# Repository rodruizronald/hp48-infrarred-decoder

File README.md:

# HP-48GX-Infrarred-Signal-Decoder

The HP 48 is a series of graphing calculators capable of communicate with a wireless printer via infrared signals. The protocol used by these calculators, called "Rey Eye", operates in a frequency of 33 kHz. This project aims to replicate a program that runs in an HP 48GX to read an electronic people counter. Reading the counters with a calculator is not practical, and therefore a specific device should be built for this task. To construct such device the project was divided into three parts.

First, the signals emitted by the calculator's program were decoded with an IR sensor conneceted to an oscilloscope and then replicated with an Atmega328p. After decoding the infrared signals, the results were examined to understand better the protocol. This examination provided the required information to code a program capable of reading the infrared signals. Finally, to implement the emitter and receiver code in a functional device, a PCB board was designed.

Although this project focuses on a specific program to read electronic people counter, it can be used as a starting point for others since the communication protocol is the same for all applications.

## Red Eye Protocol

The Red Eye Frame is composed of 15 bits:

* 1.5 start bits.   
* 4 error bits.
* 8 data bits.
* 1.5 stop bits.

Generally, the length of each bit within the frame is 854.5 us, but this value could vary depend on the IR sensor implemented. It is advisable to test with an oscilloscope the output of the sesor before making any assumptions. The logic level of one bit is defined by the position of a high state within the pulse. The high state takes 244 us, time in which the IR Led is switching on and off every 15.15 us (one cycle 30.3 us).

## Prototype

The PCB prototype contains both an IR sensor and LED to implement a bidirectional communication with the electronic counter. Additionally, a wireless LAN module was added to request and get the data remotely. The implementation of this module will be discussed in another repository to maintain this one consistent.

## Software

* Atmel Studio 6.0 - Integrated Development Platform for developing and debugging AVR microcontrollers.
* Eagle PCB Design - PCB layout and schematic design software.

## License

This project is licensed under the MIT License - see the [LICENSE.md](LICENSE.md) file for details.

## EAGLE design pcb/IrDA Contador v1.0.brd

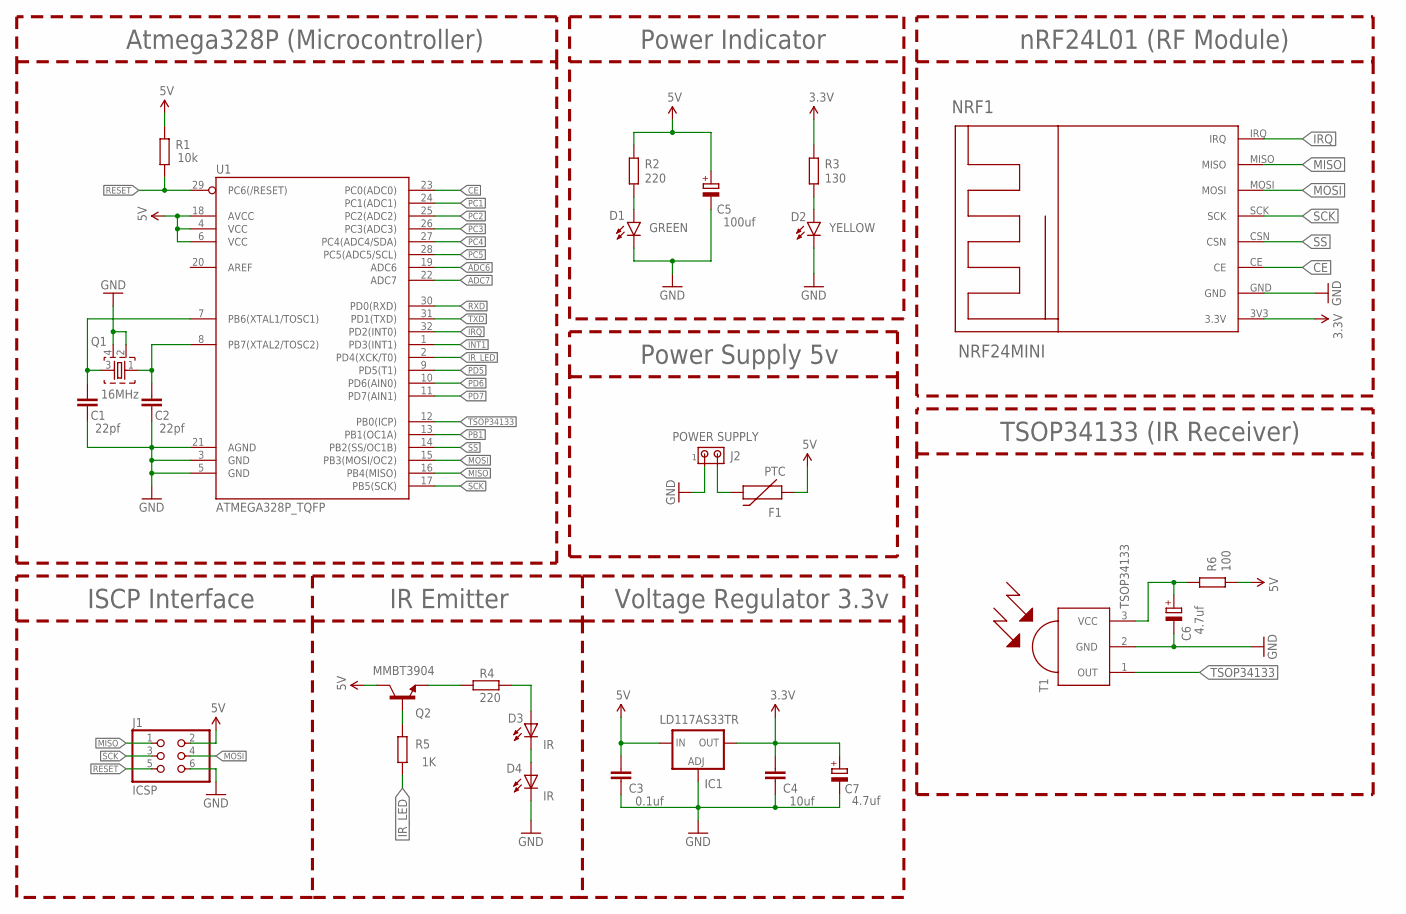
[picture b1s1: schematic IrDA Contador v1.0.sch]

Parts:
C1, C2: 22pf; C0603
C3: 0.1uf; C0603
C4: 10uf; C0603
C5: 100uf; 153CLV-0605
C6, C7: 4.7uf; SMC_A
D1: GREEN; LED-0603
D2: YELLOW; LED-0603
D3, D4: IR; LED5MM
F1: PTC; 0603
IC1: LD117AS33TR; SOT223
J1: ICSP; 2X03
J2: POWER SUPPLY; 1X2MTA
NRF1: NRF24MINI
Q1: 16MHz; FA-20H
Q2: MMBT3904; SOT23-3
R1: 10k; R0603
R2, R4: 220; R0603
R3: 130; R0603
R5: 1K; R0603
R6: 100; R0603
T1: TSOP34133
U1: ATMEGA328P_TQFP; TQFP32-08

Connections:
3.3V: C4.2, C7.+, IC1.4 (OUT), NRF1.3V3 (3.3V), R3.2
5V: C3.2, C5.+, F1.1, IC1.3 (IN), J1.2, Q2.3 (C), R1.2, R2.2, R6.1, U1.4 (VCC), U1.6 (VCC), U1.18 (AVCC)
ADC6: U1.19 (ADC6)
ADC7: U1.22 (ADC7)
CE: NRF1.CE, U1.23 (PC0(ADC0))
GND: C1.1, C2.1, C3.1, C4.1, C5.-, C6.-, C7.-, D1.C, D2.C, D4.K (C), IC1.1 (ADJ), J1.6, J2.1, NRF1.GND, Q1.2, Q1.4, T1.2 (GND), U1.3 (GND), U1.5 (GND), U1.21 (AGND)
INT1: U1.1 (PD3(INT1))
IRQ: NRF1.IRQ, U1.32 (PD2(INT0))
IR_LED: R5.2, U1.2 (PD4(XCK/T0))
MISO: J1.1, NRF1.MISO, U1.16 (PB4(MISO))
MOSI: J1.4, NRF1.MOSI, U1.15 (PB3(MOSI/OC2))
unnamed: D2.A, R3.1
unnamed: C1.2, Q1.3, U1.7 (PB6(XTAL1/TOSC1))
unnamed: C2.2, Q1.1, U1.8 (PB7(XTAL2/TOSC2))
unnamed: D1.A, R2.1
unnamed: Q2.2 (E), R4.2
unnamed: D3.A, R4.1
unnamed: D3.K (C), D4.A
unnamed: C6.+, R6.2, T1.3 (VCC)
unnamed: F1.2, J2.2
unnamed: Q2.1 (B), R5.1
PB1: U1.13 (PB1(OC1A))
PC1: U1.24 (PC1(ADC1))
PC2: U1.25 (PC2(ADC2))
PC3: U1.26 (PC3(ADC3))
PC4: U1.27 (PC4(ADC4/SDA))
PC5: U1.28 (PC5(ADC5/SCL))
PD5: U1.9 (PD5(T1))
PD6: U1.10 (PD6(AIN0))
PD7: U1.11 (PD7(AIN1))
RESET: J1.5, R1.1, U1.29 (PC6(/RESET))
RXD: U1.30 (PD0(RXD))
SCK: J1.3, NRF1.SCK, U1.17 (PB5(SCK))
SS: NRF1.CSN, U1.14 (PB2(SS/OC1B))
TSOP34133: T1.1 (OUT), U1.12 (PB0(ICP))
TXD: U1.31 (PD1(TXD))

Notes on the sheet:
nRF24L01 (RF Module)
Atmega328P (Microcontroller)
TSOP34133 (IR Receiver)
ISCP Interface
Power Supply 5v
Voltage Regulator 3.3v
Power Indicator
IR Emitter

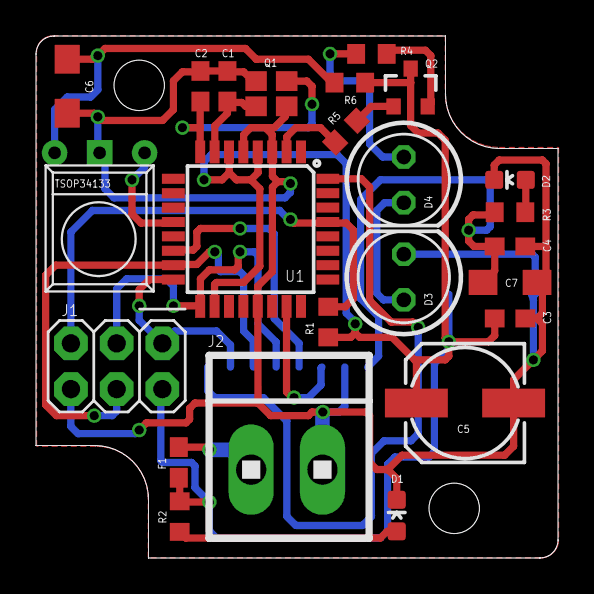
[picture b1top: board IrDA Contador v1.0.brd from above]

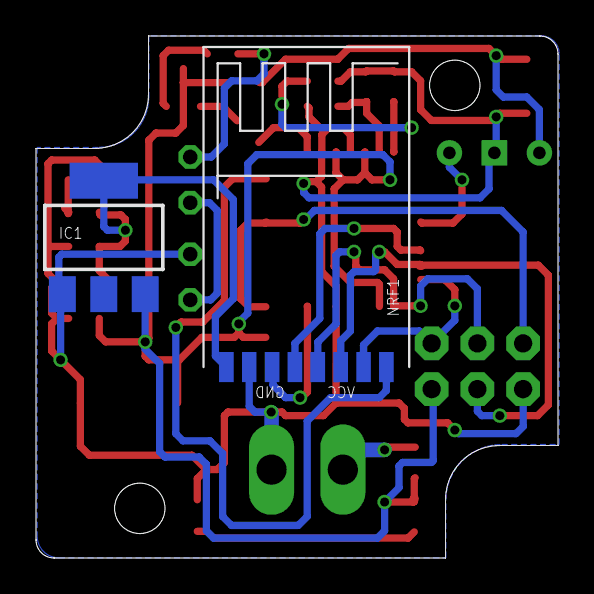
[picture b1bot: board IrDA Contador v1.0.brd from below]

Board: 2 copper layers, 29.0 x 29.0 mm, 26 parts (2 on the bottom side), 22 nets.

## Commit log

2018-11-23 IR Reciever
2018-11-23 Documentation
2018-11-24 Image Resize
2018-11-24 Resize
2018-11-24 Emitter

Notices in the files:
parts and their libraries:
SparkFun-Connectors: Licensing: Creative Commons ShareAlike 4.0 International - https://creativecommons.org/licenses/by-sa/4.0
